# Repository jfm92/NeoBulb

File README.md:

#NeoBulb

Detailed instructions:
http://www.instructables.com/id/NeoBulb-Neopixel-Bulb-With-Sensor/

This project was done for 'Creative Electronics', a Beng Electronics Engineering 4th year module at the University of Málaga, School of Telecommunications. (www.etsit.uma.es).

This project is a bulb with Bluetooth communication that can change colour brightness and create special effects with lights powered by 2 Neopixel Rings, it also has the possibility to connect a external sensor to measure outside parameters like temperature, humidity, move...

And a special fact, that is quite important nowadays, is that it onlyconsumes around 4W a maximum in white and with maximum luminosity.

Every parameter is controlled by an Android APP, that shows:

The mesure of the humidity and the temperature of the room in which the bulb is
Change the colour of the bulb.
To Program the default colour of the bulb that is an option if you want to use like a regular bulb.
Special lights effects , like an Aurora, light of a candle or random colors every 5 sec.
All the circuits are embedded in a regular bulb of 15W of which I only used the body.

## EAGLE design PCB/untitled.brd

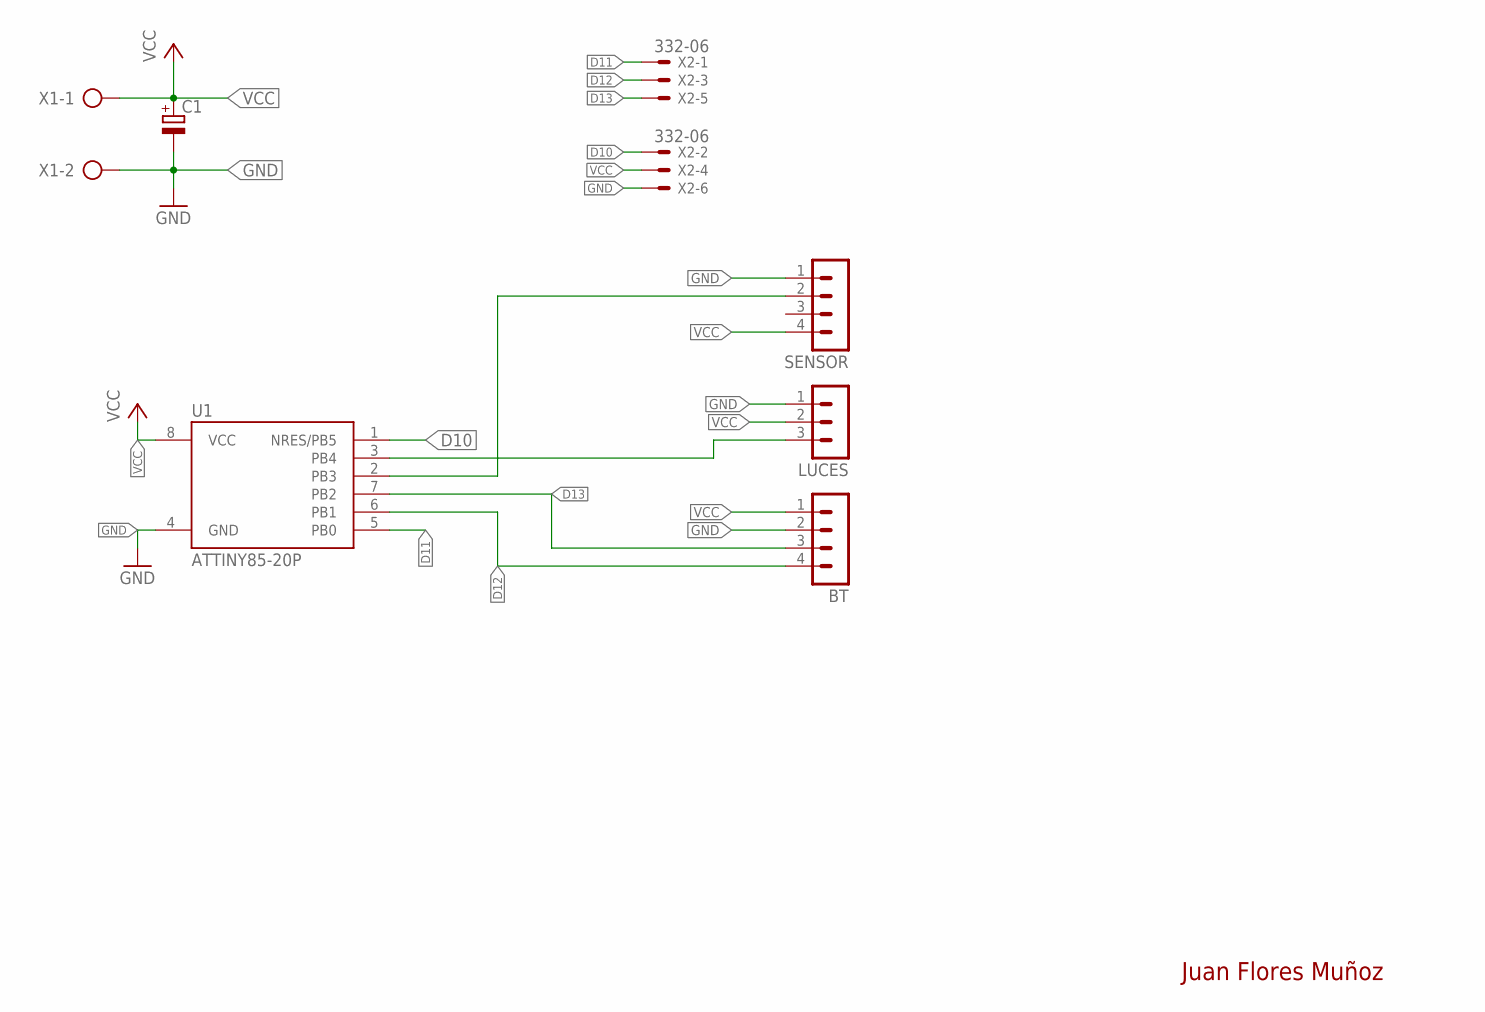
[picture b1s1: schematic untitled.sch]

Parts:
BT: MA04-1
C1: CPOL-EUE2,5-6E; E2,5-6E
LUCES: MA03-1
SENSOR: MA04-1
U1: ATTINY85-20P; PDIP08_300MIL
X1: AK500/2
X2: 332-06

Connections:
01: SENSOR.2, U1.2 (PB3)
D10: U1.1 (NRES/PB5), X2.2
D11: U1.5 (PB0), X2.1
D12: BT.4, U1.6 (PB1), X2.3
D13: BT.3, U1.7 (PB2), X2.5
GND: BT.2, C1.-, LUCES.1, SENSOR.1, U1.4 (GND), X1.2, X2.6
unnamed: LUCES.3, U1.3 (PB4)
VCC: BT.1, C1.+, LUCES.2, SENSOR.4, U1.8 (VCC), X1.1, X2.4

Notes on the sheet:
Juan Flores Muñoz

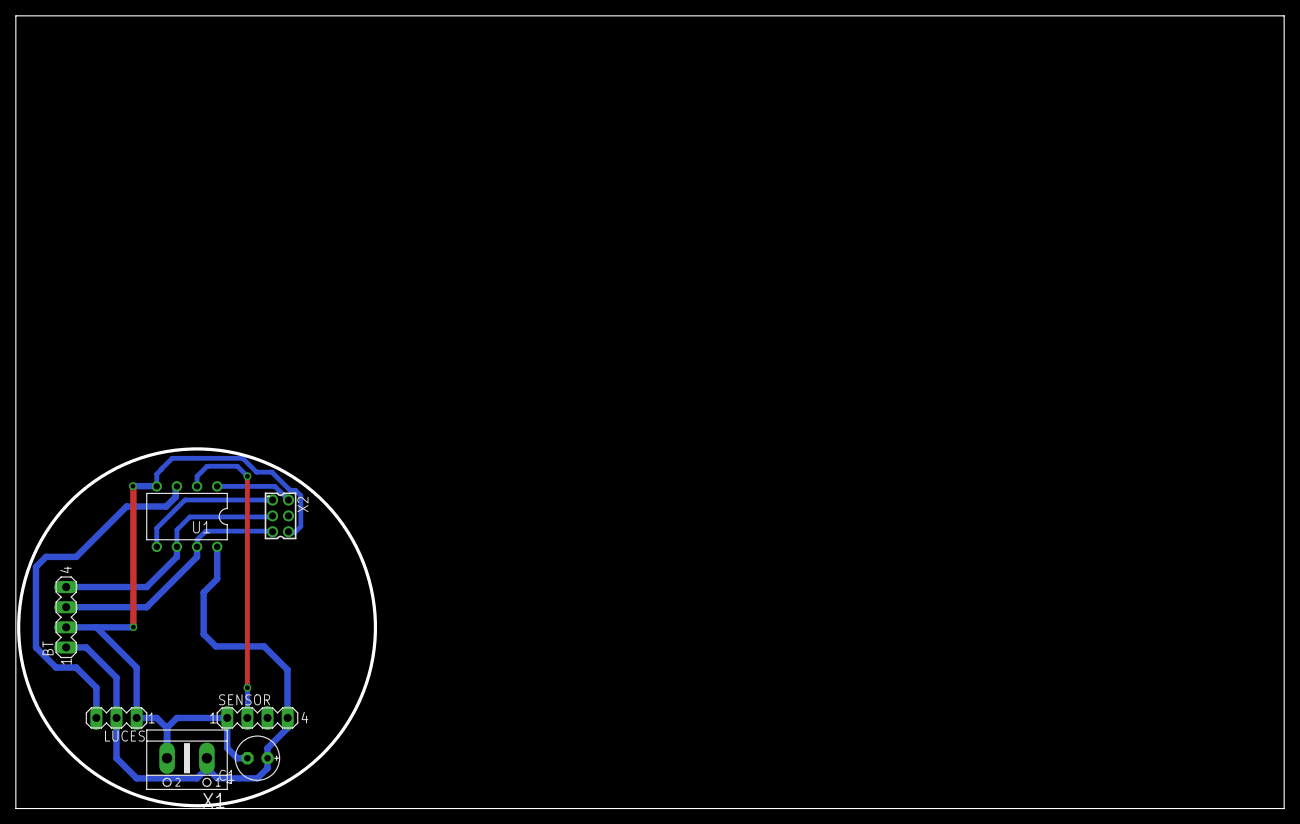
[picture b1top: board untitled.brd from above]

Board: 2 copper layers, 160.0 x 100.0 mm, 7 parts (0 on the bottom side), 8 nets.

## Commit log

2017-02-01 NeoBulbCommit
2017-02-01 This is the first version of the NeoBulb project
2017-02-01 Update README.md
    Description of the NeoBulb and link to the full instructions
